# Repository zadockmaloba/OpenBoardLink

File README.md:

An open, low-cost ARM SWD programmer/debugger built around an STM32F103C8 running Zephyr RTOS. Rev 1, October 2026.

## Hardware

Schematic: `./hardware/USB2SWD.kicad_sch` (KiCad 10).

## Firmware

**NOTE:** 
- CH340P/FTDI drivers required for serial communication.
    - See: https://sparks.gogo.co.nz/ch340.html?srsltid=AYCX9vJ7uKf6C0Zw0mtyxMH3N8wv1fY7HUsu3qdjR-UEwpCyX_hEoPqb

- STM32CubeProgrammer is currently required to flash firmware to the programmer.
    - See: https://www.st.com/en/development-tools/stm32cubeprog.html

Zephyr 4.3.0 with a custom board definition (`openboardlink`, SoC `stm32f103xb`).

Build:

```
cd firmware
west build -p always -b openboardlink/stm32f103xb
```

Requires west, CMake and the Zephyr SDK 0.17.x.

## Snapshots

### Rev-1 (v0.5) 4-Nov-2026
![][rev-1.0.5]

[rev-1.0.5]: ./snapshots/REV-1-v0.5.png

### Rev-1 (v0.4) 1-Nov-2026
![][rev-1.0.4]

[rev-1.0.4]: ./snapshots/REV-1-v0.4.png

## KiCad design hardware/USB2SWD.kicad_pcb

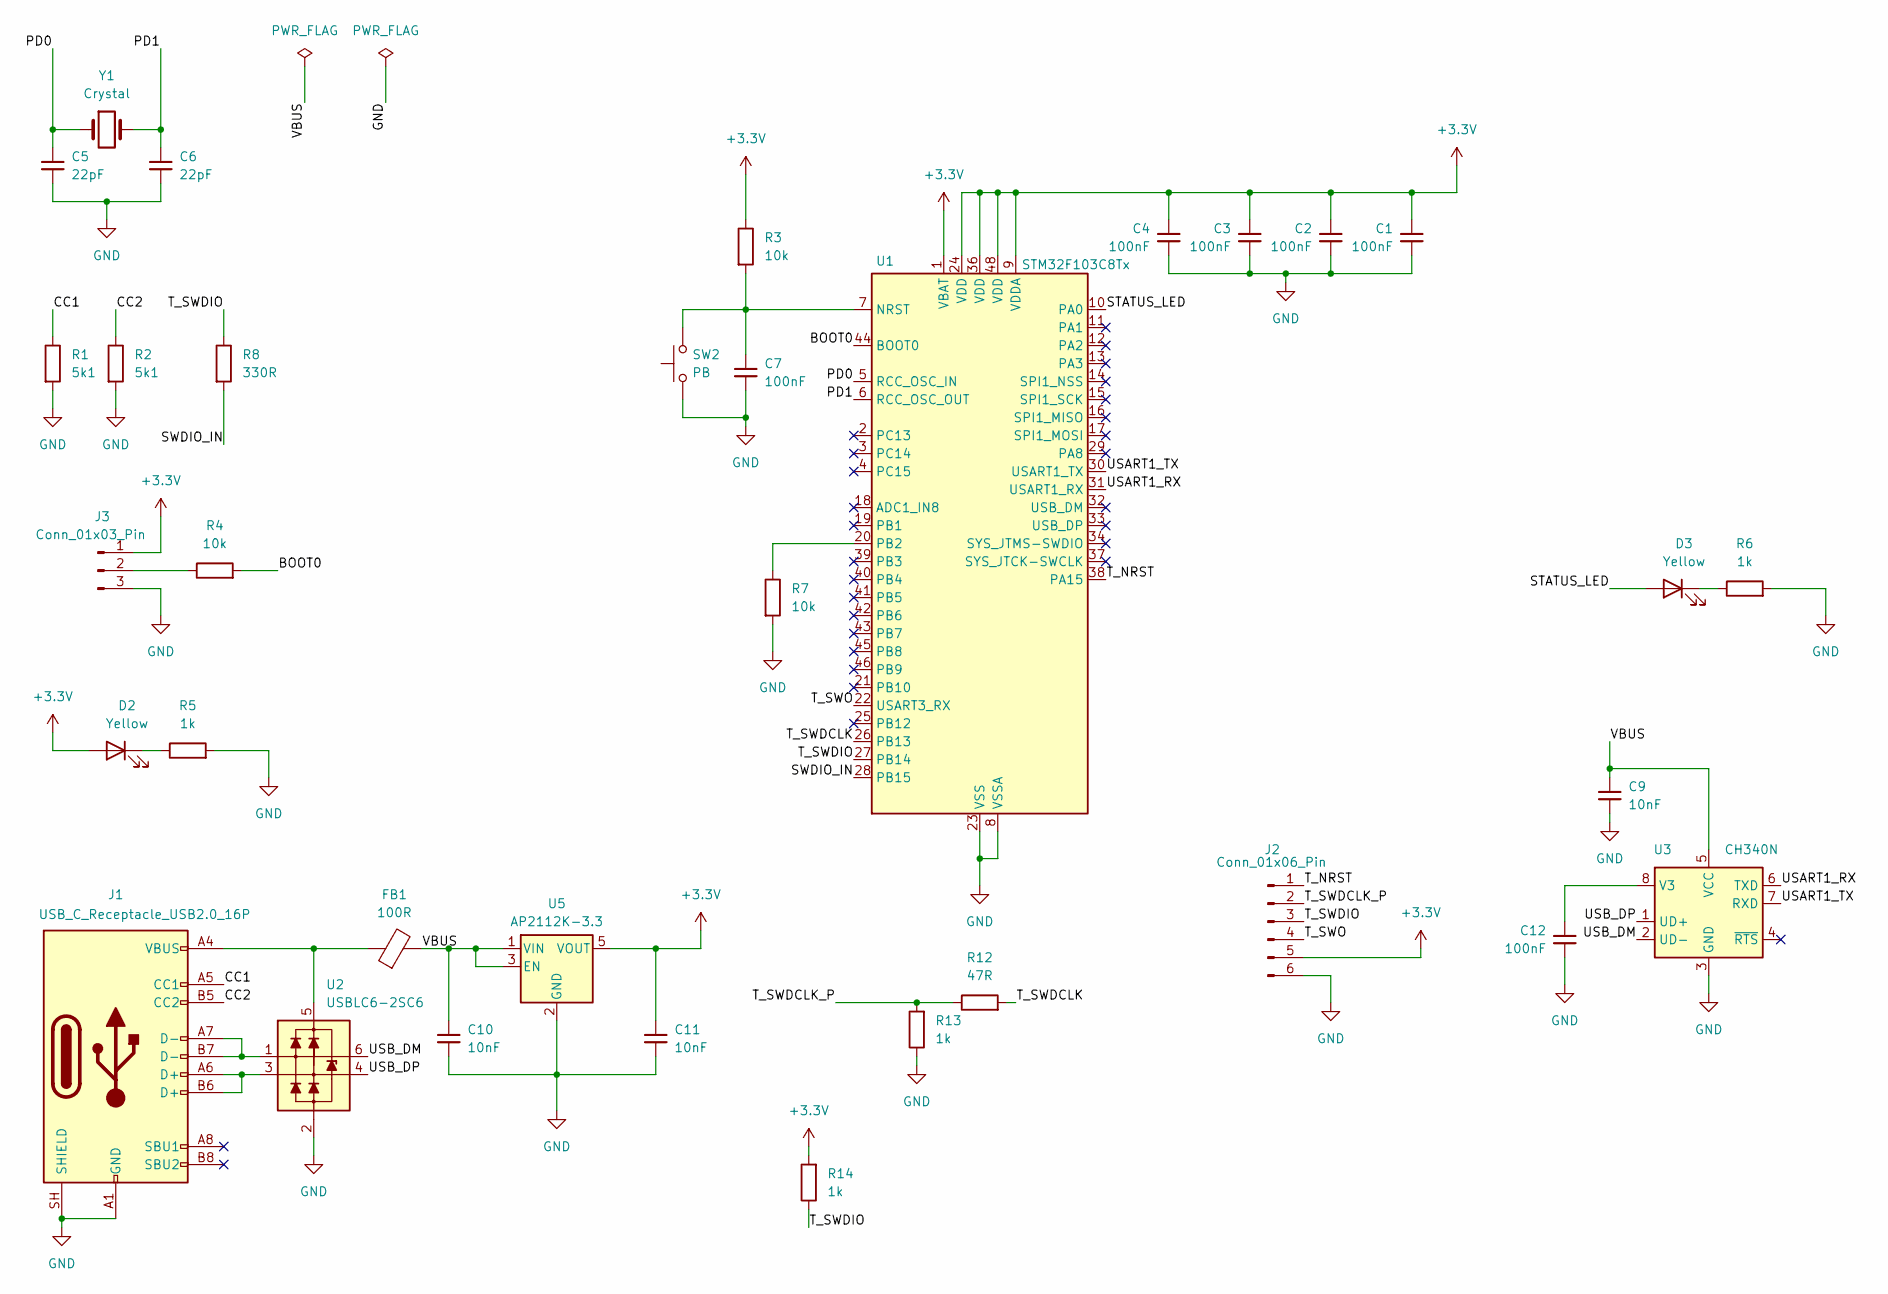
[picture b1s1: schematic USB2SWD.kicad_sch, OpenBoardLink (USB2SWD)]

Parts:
C1, C2, C3, C4, C7, C12: 100nF; C_0805_2012Metric_Pad1.18x1.45mm_HandSolder; LCSC C28233
C5, C6: 22pF; C_0805_2012Metric_Pad1.18x1.45mm_HandSolder; LCSC C1804
C9, C10, C11: 10nF; C_0805_2012Metric_Pad1.18x1.45mm_HandSolder; LCSC C1710
D2, D3: Yellow; LED_0805_2012Metric_Pad1.15x1.40mm_HandSolder; LCSC C2296
FB1: 100R; L_0805_2012Metric_Pad1.05x1.20mm_HandSolder; LCSC C1015
J1: USB_C_Receptacle_USB2.0_16P; USB_C_Receptacle_GCT_USB4105-xx-A_16P_TopMnt_Horizontal; LCSC C27636760
J2: Conn_01x06_Pin; PinHeader_1x06_P2.54mm_Vertical; LCSC C32713272
J3: Conn_01x03_Pin; PinHeader_1x03_P2.54mm_Vertical
R1, R2: 5k1; R_0805_2012Metric_Pad1.20x1.40mm_HandSolder; LCSC C27834
R3, R4, R7: 10k; R_0805_2012Metric_Pad1.20x1.40mm_HandSolder; LCSC C17414
R5, R6, R13, R14: 1k; R_0805_2012Metric_Pad1.20x1.40mm_HandSolder; LCSC C17513
R8: 330R; R_0805_2012Metric_Pad1.20x1.40mm_HandSolder; LCSC C17630
R12: 47R; R_0805_2012Metric_Pad1.20x1.40mm_HandSolder; LCSC C17714
SW2: PB; SW_Push_1P1T_NO_CK_KMR2; LCSC C556652
U1: STM32F103C8Tx; LQFP-48_7x7mm_P0.5mm; LCSC C8734
U2: USBLC6-2SC6; SOT-23-6; LCSC C6807798
U3: CH340N; JEITA_SOIC-8_3.9x4.9mm_P1.27mm; LCSC C2977777
U5: AP2112K-3.3; SOT-23-5; LCSC C3021085
Y1: Crystal; Crystal_HC49-4H_Vertical; LCSC C326536

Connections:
+3.3V: C1.1, C2.1, C3.1, C4.1, C11.1, D2.2 (A), J2.5, J3.1, R3.1, R14.2, U1.1 (VBAT), U1.9 (VDDA), U1.24 (VDD), U1.36 (VDD), U1.48 (VDD), U5.5 (VOUT)
/BOOT0: R4.2, U1.44 (BOOT0)
/CC1: J1.A5 (CC1), R1.1
/CC2: J1.B5 (CC2), R2.1
/PD0: C5.1, U1.5 (RCC_OSC_IN), Y1.1
/PD1: C6.1, U1.6 (RCC_OSC_OUT), Y1.2
/STATUS_LED: D3.2 (A), U1.10 (PA0)
/SWDIO_IN: R8.2, U1.28 (PB15)
/T_NRST: J2.1, U1.38 (PA15)
/T_SWDCLK: R12.2, U1.26 (PB13)
/T_SWDCLK_P: J2.2, R12.1, R13.2
/T_SWDIO: J2.3, R8.1, R14.1, U1.27 (PB14)
/T_SWO: J2.4, U1.22 (USART3_RX)
/USART1_RX: U1.31 (USART1_RX), U3.6 (TXD)
/USART1_TX: U1.30 (USART1_TX), U3.7 (RXD)
/USB_DM: U2.6 (L1), U3.2 (UD-)
/USB_DP: U2.4 (L2), U3.1 (UD+)
/VBUS: C9.1, C10.1, FB1.2, U3.5 (VCC), U5.1 (VIN), U5.3 (EN)
GND: C1.2, C2.2, C3.2, C4.2, C5.2, C6.2, C7.2, C9.2, C10.2, C11.2, C12.2, J1.A1 (GND), J1.A12 (GND), J1.B1 (GND), J1.B12 (GND), J1.SH (SHIELD), J2.6, J3.3, R1.2, R2.2, R5.2, R6.2, R7.2, R13.1, SW2.1, U1.8 (VSSA), U1.23 (VSS), U1.35 (VSS), U1.47 (VSS), U2.2 (VN), U3.3 (GND), U5.2 (GND)
unnamed: D2.1 (K), R5.1
unnamed: D3.1 (K), R6.1
unnamed: J1.A6 (D+), J1.B6 (D+), U2.3 (L2)
unnamed: J1.A7 (D-), J1.B7 (D-), U2.1 (L1)
unnamed: J3.2, R4.1
unnamed: C7.1, R3.2, SW2.2, U1.7 (NRST)
unnamed: R7.1, U1.20 (PB2)
unnamed: FB1.1, J1.A4 (VBUS), J1.A9 (VBUS), J1.B4 (VBUS), J1.B9 (VBUS), U2.5 (VP)
unnamed: C12.1, U3.8 (V3)

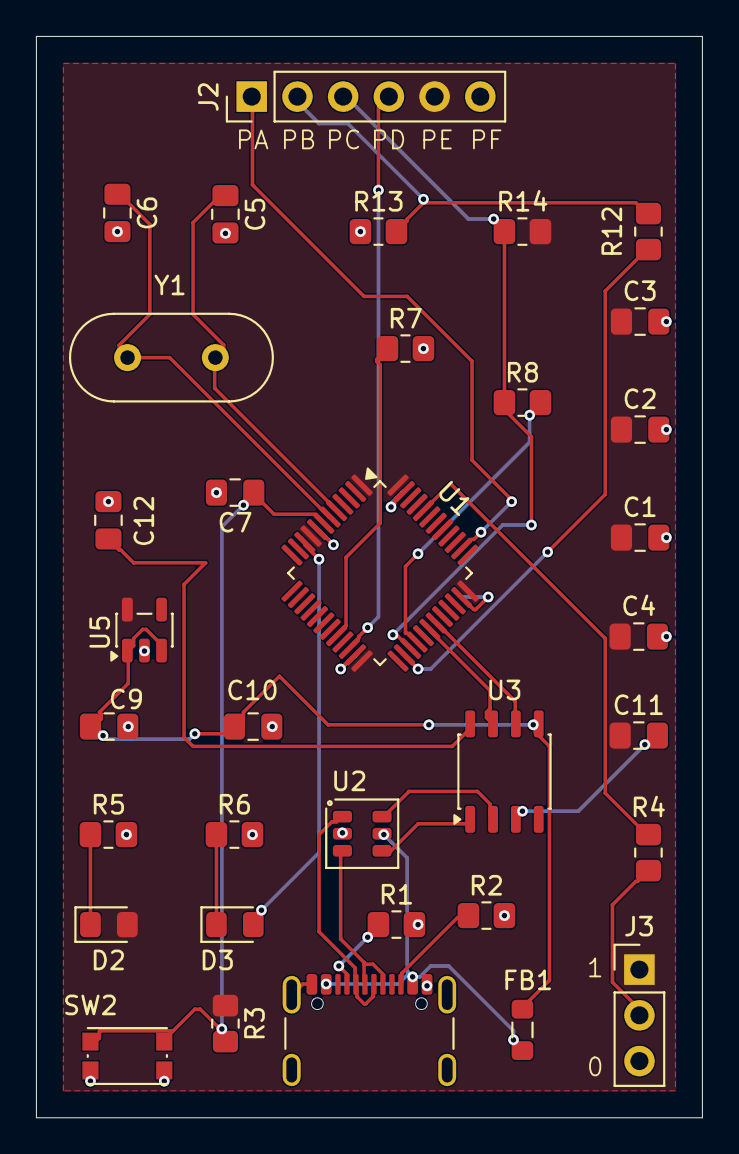
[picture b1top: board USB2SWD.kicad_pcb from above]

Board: 2 copper layers, 37.0 x 60.1 mm, 34 parts (0 on the bottom side), 28 nets.

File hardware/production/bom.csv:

Designator,Footprint,Quantity,Value,LCSC Part #
"C1, C12, C2, C3, C4, C7",0805,6,100nF,C28233
"C10, C11, C9",0805,3,10nF,C1710
"C5, C6",0805,2,22pF,C1804
"D2, D3",0805,2,Yellow,C2296
FB1,0805,1,100R,C1015
"R1, R2",0805,2,5k1,C27834
R12,0805,1,47R,C17714
"R13, R14, R5, R6",0805,4,1k,C17513
"R3, R4, R7",0805,3,10k,C17414
R8,0805,1,330R,C17630
U1,LQFP-48_7x7mm_P0.5mm,1,STM32F103C8Tx,C8734
U2,SOT-23-6,1,USBLC6-2SC6,C6807798
U3,JEITA_SOIC-8_3.9x4.9mm_P1.27mm,1,CH340N,C2977777
U5,SOT-23-5,1,AP2112K-3.3,C3021085
Y1,Crystal_HC49-4H_Vertical,1,Crystal,C326536
